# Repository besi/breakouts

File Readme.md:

# Breakouts

Some custom breakout boards

## AMS117

# TODO

- Omron Relay
- Stepper connector
- ULN2003

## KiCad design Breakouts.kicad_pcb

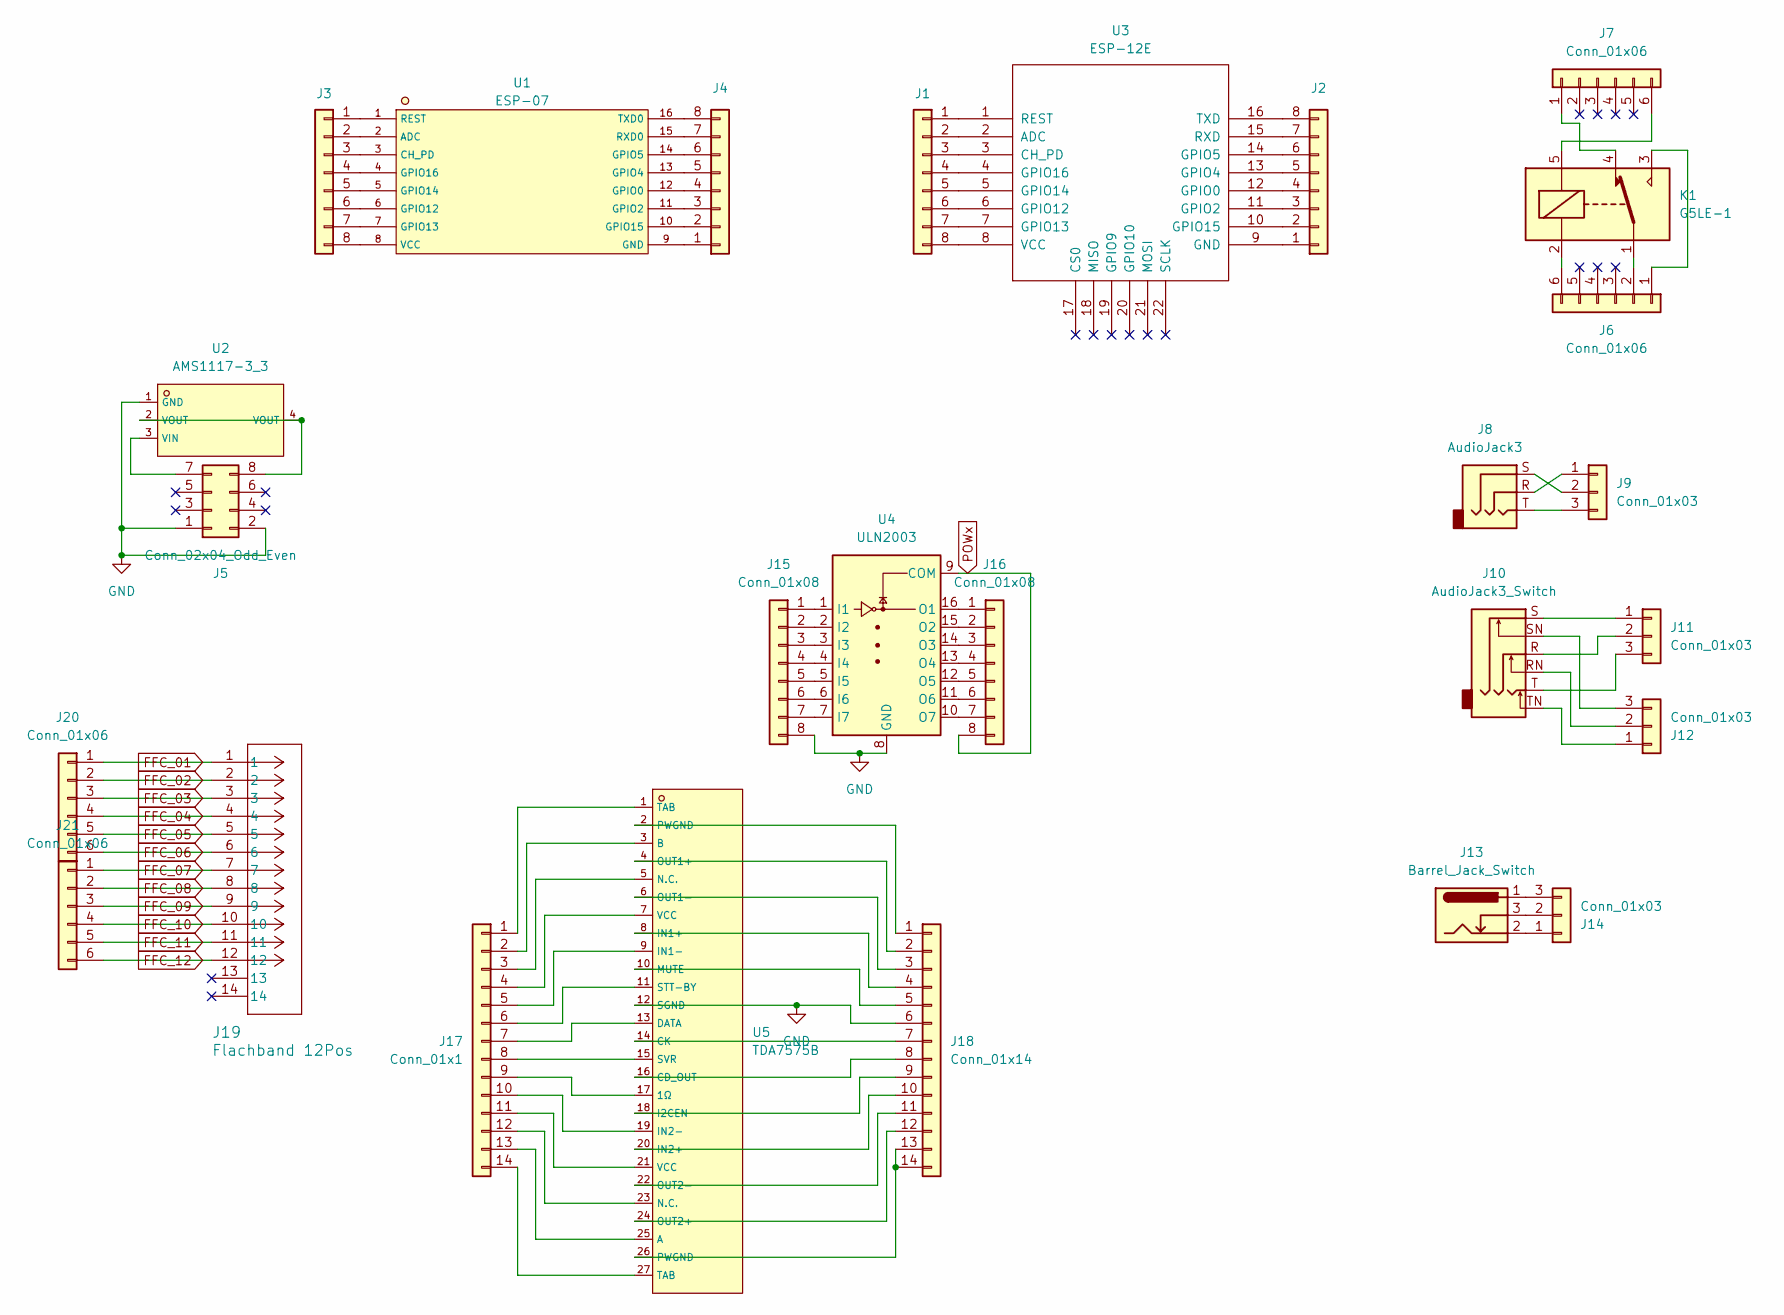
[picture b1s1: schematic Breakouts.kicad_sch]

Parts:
J1, J2, J3, J4: Conn_01x08; PinHeader_1x08_P2.54mm_Vertical
J5: Conn_02x04_Odd_Even; PinHeader_2x04_P2.54mm_Vertical
J6, J7, J20, J21: Conn_01x06; PinHeader_1x06_P2.54mm_Vertical
J8: AudioJack3; Jack_3.5mm_CUI_SJ-3523-SMT_Horizontal
J9: Conn_01x03; PinHeader_1x03_P2.54mm_Vertical
J10: AudioJack3_Switch; Jack_6.35mm_Neutrik_NMJ6HFD2_Horizontal
J11, J12, J14: Conn_01x03; PinHeader_1x03_P2.54mm_Vertical_SMD_Pin1Left
J13: Barrel_Jack_Switch; BarrelJack_GCT_DCJ200-10-A_Horizontal
J15, J16: Conn_01x08; PinHeader_1x08_P2.00mm_Vertical
J17: Conn_01x1; PinHeader_1x14_P2.54mm_Vertical
J18: Conn_01x14; PinHeader_1x14_P2.54mm_Vertical
J19: Flachband 12Pos; CONN12_1-1734742-2_TEC
K1: G5LE-1; Relay_SPDT_Omron-G5LE-1
U1: ESP-07; WIFIM-SMD_ESP-07; LCSC C82894
U2: AMS1117-3_3; SOT-223-3_L6.5-W3.4-P2.30-LS7.0-BR; LCSC C6186
U3: ESP-12E; WIFIM-SMD_ESP-07
U4: ULN2003; SOIC-16W_5.3x10.2mm_P1.27mm
U5: TDA7575B; FLEXIWATT27-TH_27P-L29.3-W4.6-P1.00; LCSC C843553

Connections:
FFC_01: J19.1, J20.1
FFC_02: J19.2, J20.2
FFC_03: J19.3, J20.3
FFC_04: J19.4, J20.4
FFC_05: J19.5, J20.5
FFC_06: J19.6, J20.6
FFC_07: J19.7, J21.1
FFC_08: J19.8, J21.2
FFC_09: J19.9, J21.3
FFC_10: J19.10, J21.4
FFC_11: J19.11, J21.5
FFC_12: J19.12, J21.6
GND: J5.1, J5.2, J15.8, J18.6, U2.1 (GND), U4.8 (GND), U5.12 (SGND)
unnamed: J1.1, U3.1 (REST)
unnamed: J1.2, U3.2 (ADC)
unnamed: J1.3, U3.3 (CH_PD)
unnamed: J1.4, U3.4 (GPIO16)
unnamed: J1.5, U3.5 (GPIO14)
unnamed: J1.6, U3.6 (GPIO12)
unnamed: J1.7, U3.7 (GPIO13)
unnamed: J1.8, U3.8 (VCC)
unnamed: J2.1, U3.9 (GND)
unnamed: J2.2, U3.10 (GPIO15)
unnamed: J2.3, U3.11 (GPIO2)
unnamed: J2.4, U3.12 (GPIO0)
unnamed: J2.5, U3.13 (GPIO4)
unnamed: J2.6, U3.14 (GPIO5)
unnamed: J2.7, U3.15 (RXD)
unnamed: J2.8, U3.16 (TXD)
unnamed: J3.1, U1.1 (REST)
unnamed: J3.2, U1.2 (ADC)
unnamed: J3.3, U1.3 (CH_PD)
unnamed: J3.4, U1.4 (GPIO16)
unnamed: J3.5, U1.5 (GPIO14)
unnamed: J3.6, U1.6 (GPIO12)
unnamed: J3.7, U1.7 (GPIO13)
unnamed: J3.8, U1.8 (VCC)
unnamed: J4.1, U1.9 (GND)
unnamed: J4.2, U1.10 (GPIO15)
unnamed: J4.3, U1.11 (GPIO2)
unnamed: J4.4, U1.12 (GPIO0)
unnamed: J4.5, U1.13 (GPIO4)
unnamed: J4.6, U1.14 (GPIO5)
unnamed: J4.7, U1.15 (RXD0)
unnamed: J4.8, U1.16 (TXD0)
unnamed: J5.7, U2.3 (VIN)
unnamed: J5.8, U2.2 (VOUT), U2.4 (VOUT)
unnamed: J6.1, K1.3
unnamed: J6.2, K1.1
unnamed: J6.6, K1.2
unnamed: J7.1, K1.4
unnamed: J7.6, K1.5
unnamed: J8.R, J9.1
unnamed: J8.S, J9.2
unnamed: J8.T, J9.3
unnamed: J10.S, J11.1
unnamed: J10.R, J11.2
unnamed: J10.T, J11.3
unnamed: J10.TN, J12.1
unnamed: J10.RN, J12.2
unnamed: J10.SN, J12.3
unnamed: J13.2, J14.1
unnamed: J13.3, J14.2
unnamed: J13.1, J14.3
unnamed: J15.1, U4.1 (I1)
unnamed: J15.2, U4.2 (I2)
unnamed: J15.3, U4.3 (I3)
unnamed: J15.4, U4.4 (I4)
unnamed: J15.5, U4.5 (I5)
unnamed: J15.6, U4.6 (I6)
unnamed: J15.7, U4.7 (I7)
unnamed: J16.1, U4.16 (O1)
unnamed: J16.2, U4.15 (O2)
unnamed: J16.3, U4.14 (O3)
unnamed: J16.4, U4.13 (O4)
unnamed: J16.5, U4.12 (O5)
unnamed: J16.6, U4.11 (O6)
unnamed: J16.7, U4.10 (O7)
unnamed: J17.1, U5.1 (TAB)
unnamed: J17.2, U5.3 (B)
unnamed: J17.3, U5.5 (N.C.)
unnamed: J17.4, U5.7 (VCC)
unnamed: J17.5, U5.9 (IN1-)
unnamed: J17.6, U5.11 (STT-BY)
unnamed: J17.7, U5.13 (DATA)
unnamed: J17.8, U5.15 (SVR)
unnamed: J17.9, U5.17 (1Ω)
unnamed: J17.10, U5.19 (IN2-)
unnamed: J17.11, U5.21 (VCC)
unnamed: J17.12, U5.23 (N.C.)
unnamed: J17.13, U5.25 (A)
unnamed: J17.14, U5.27 (TAB)
unnamed: J18.1, U5.2 (PWGND)
unnamed: J18.2, U5.4 (OUT1+)
unnamed: J18.3, U5.6 (OUT1-)
unnamed: J18.4, U5.8 (IN1+)
unnamed: J18.5, U5.10 (MUTE)
unnamed: J18.7, U5.14 (CK)
unnamed: J18.8, U5.16 (CD_OUT)
unnamed: J18.9, U5.18 (I2CEN)
unnamed: J18.10, U5.20 (IN2+)
unnamed: J18.11, U5.22 (OUT2-)
unnamed: J18.12, U5.24 (OUT2+)
unnamed: J18.13, J18.14, U5.26 (PWGND)
POWx: J16.8, U4.9 (COM)

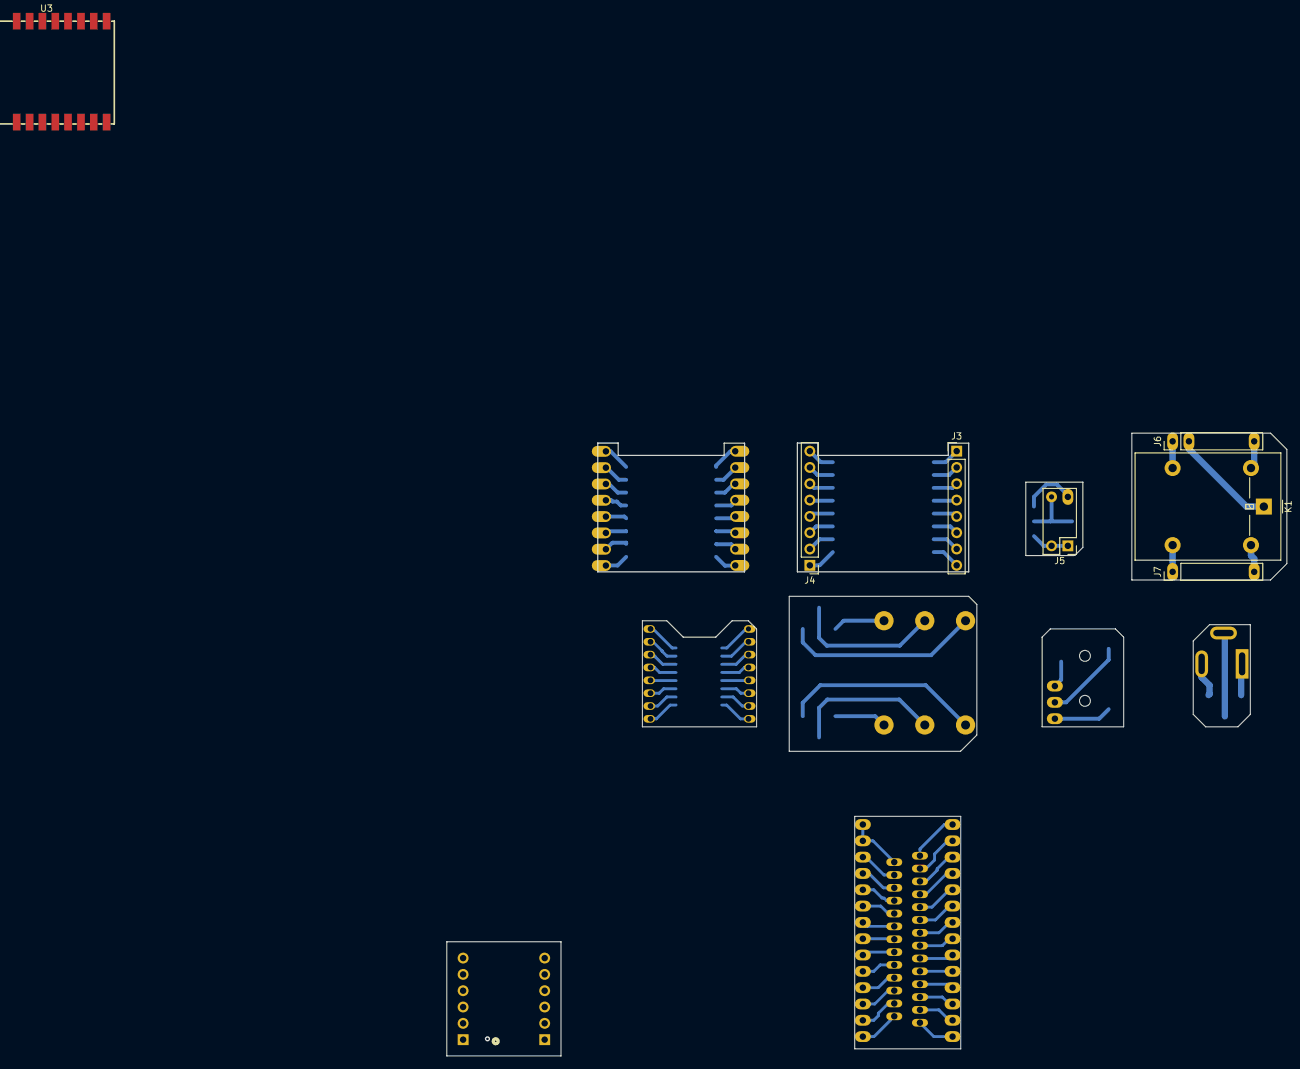
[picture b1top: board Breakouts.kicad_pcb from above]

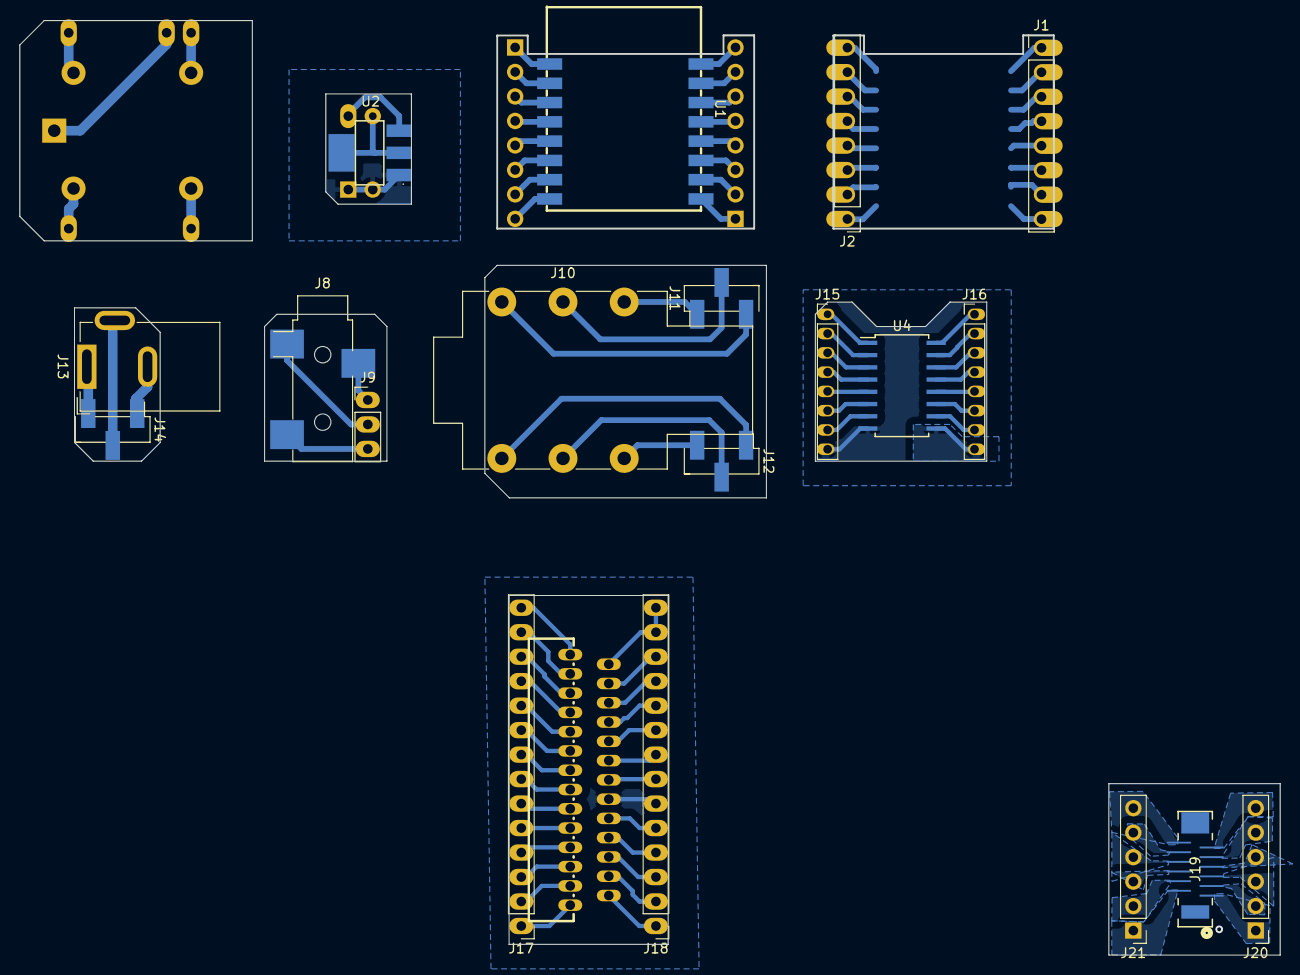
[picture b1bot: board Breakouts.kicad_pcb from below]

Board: 2 copper layers, 130.7 x 96.9 mm, 27 parts (20 on the bottom side), 105 nets.

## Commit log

2024-03-12 Add AMS117
2024-03-12 Add preliminary esp07
2024-03-12 Added todos
2024-03-12 Added relay breakout
2024-03-13 Add audio jack
2024-03-13 Bigger pads
2024-03-13 big audio jack
2024-03-13 Add barrel jack
2024-03-13 Add ULN2003 breakout
2024-03-13 Add ULN2003 breakout with copper pour
2024-03-13 Add screenshot
2024-03-13 re-arrange pcbs
2024-04-23 Add FCC pos12 cable breakout
2024-04-23 Add schematic for pos18 ffc cable
2024-07-18 Add TDA7575B Breakout
